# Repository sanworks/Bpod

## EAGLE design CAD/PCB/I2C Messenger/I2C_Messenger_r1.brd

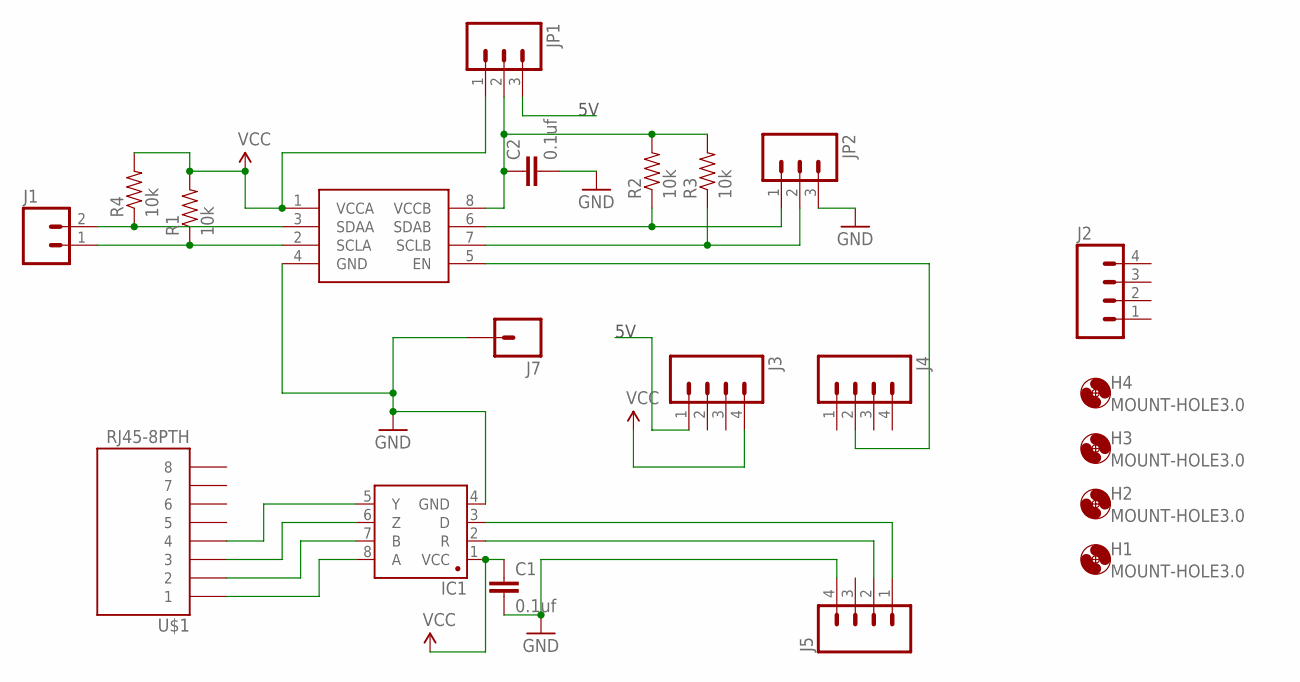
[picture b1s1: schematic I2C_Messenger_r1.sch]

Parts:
C1, C2: 0.1uf; 1206
H1, H2, H3, H4: MOUNT-HOLE3.0; 3,0
IC1: SN65HVD31DR; SO08
IC2: PCA9517; SO-08
J1: M02PTH; 1X02
J2, J3, J4, J5: M04PTH; 1X04
J7: M01PTH; 1X01
JP1: M03PTH; 1X03
JP2: M03SCREW_LOCK; SCREWTERMINAL-3.5MM-3_LOCK.007S
R1, R2, R3, R4: 10k; 1206
U$1: RJ45-8PTH; RJ45-8

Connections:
5V: J3.1, JP1.3
GND: C1.2, C2.2, IC1.4 (GND), IC2.4 (GND), J5.4, J7.1, JP2.3
unnamed: IC1.3 (D), J5.1
unnamed: IC2.2 (SCLA), J1.1, R1.1
unnamed: IC1.2 (R), J5.2
unnamed: IC1.8 (A), U$1.1
unnamed: IC1.7 (B), U$1.2
unnamed: IC1.6 (Z), U$1.3
unnamed: IC1.5 (Y), U$1.4
unnamed: IC2.3 (SDAA), J1.2, R4.1
unnamed: C2.1, IC2.8 (VCCB), JP1.2, R2.2, R3.2
unnamed: IC2.5 (EN), J4.2
unnamed: IC2.6 (SDAB), JP2.1, R2.1
unnamed: IC2.7 (SCLB), JP2.2, R3.1
VCC: C1.1, IC1.1 (VCC), IC2.1 (VCCA), J3.4, JP1.1, R1.2, R4.2

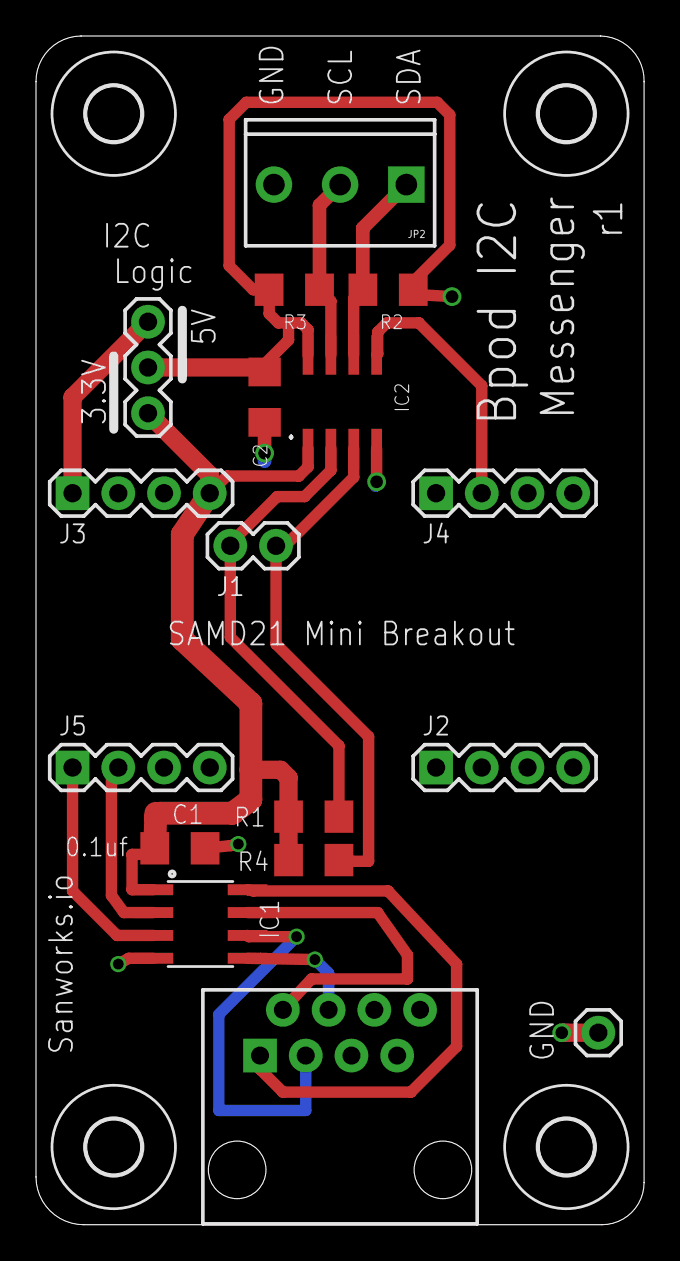
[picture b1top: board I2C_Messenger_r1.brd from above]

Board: 2 copper layers, 33.8 x 66.0 mm, 21 parts (0 on the bottom side), 15 nets.

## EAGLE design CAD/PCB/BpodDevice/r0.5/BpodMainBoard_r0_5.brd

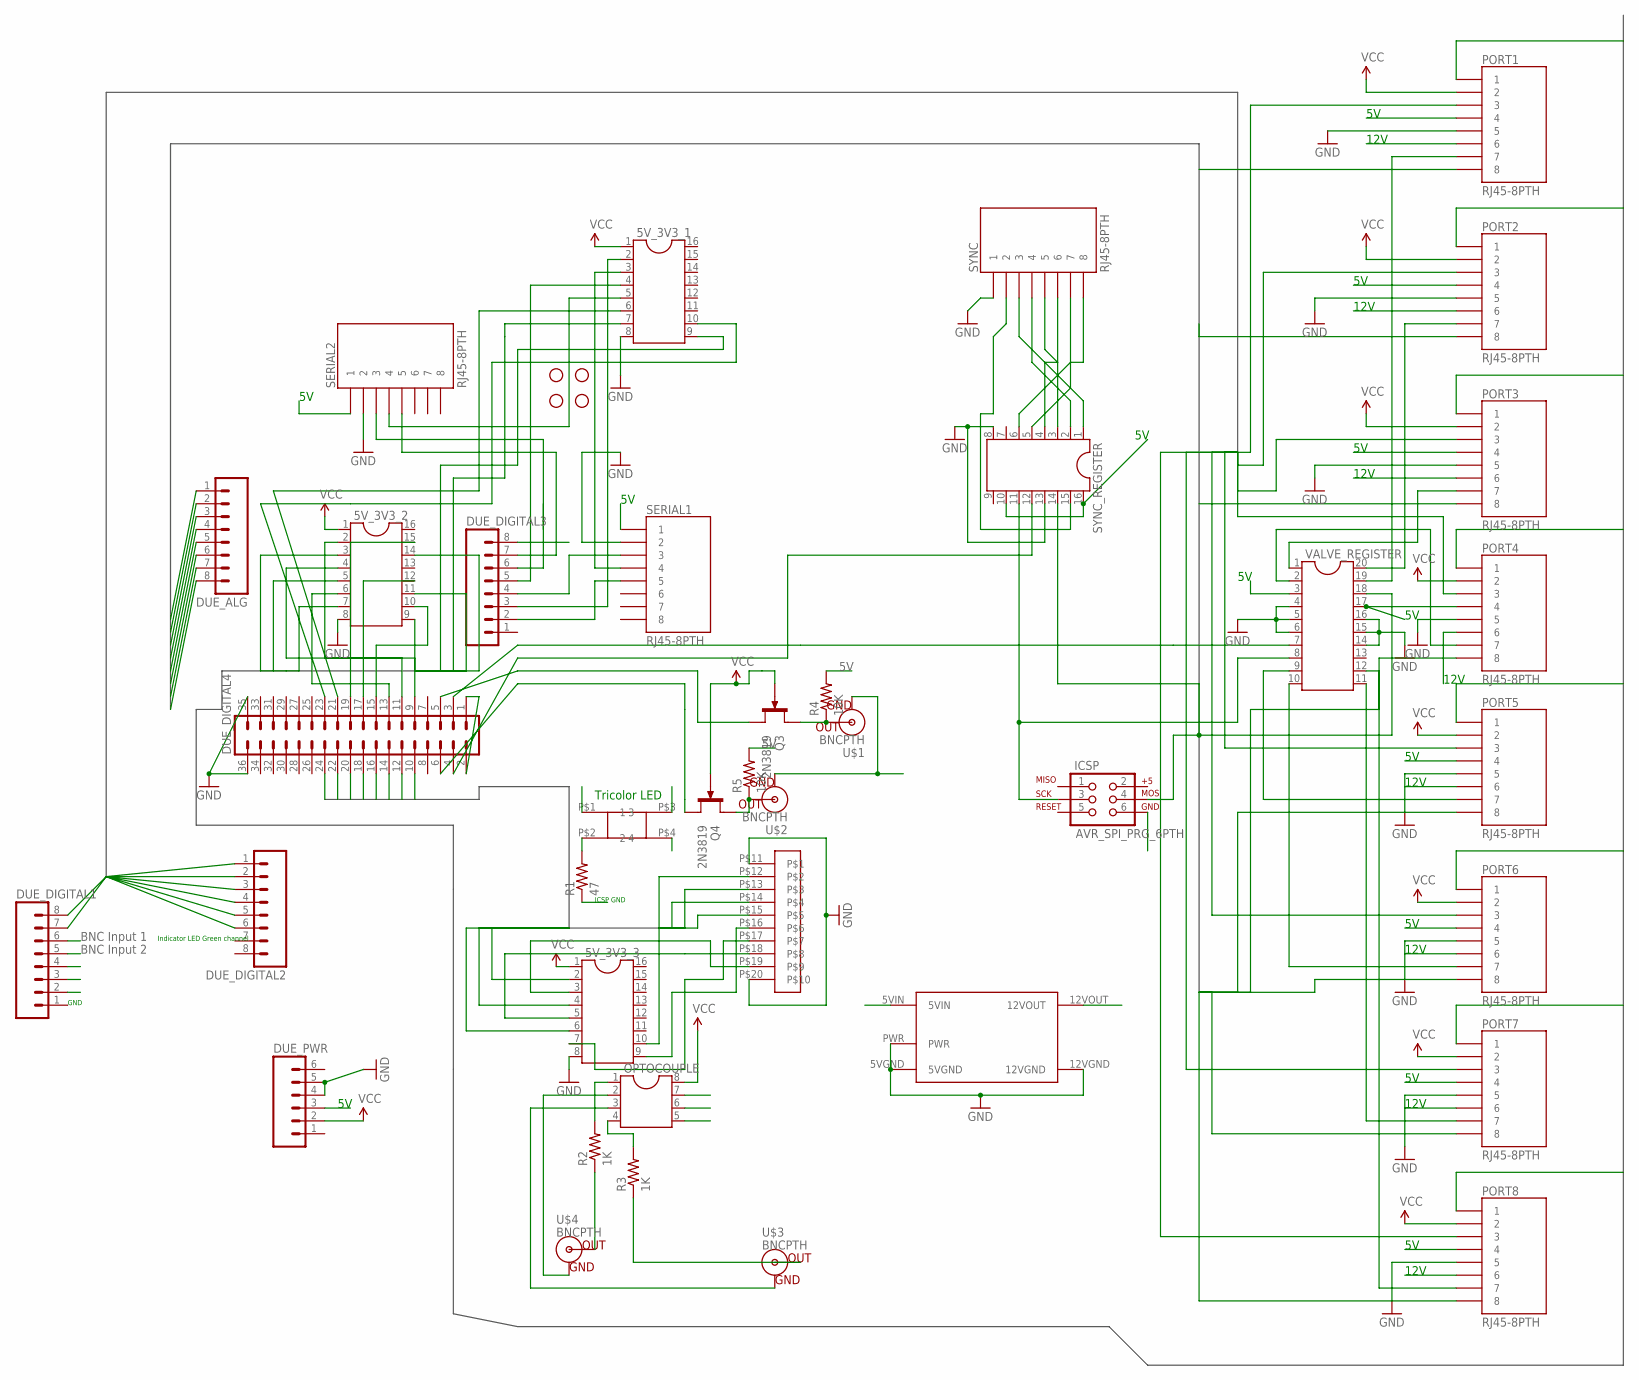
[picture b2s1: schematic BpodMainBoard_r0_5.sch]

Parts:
5V_3V3_1, 5V_3V3_2, 5V_3V3_3: DIL16
DUE_ALG: M081X08; 1X08
DUE_DIGITAL1, DUE_DIGITAL2, DUE_DIGITAL3: M081X08; 1X08
DUE_DIGITAL4: MA18-2
DUE_PWR: M06SIP; 1X06
ICSP: AVR_SPI_PRG_6PTH; 2X3
JP1, JP2, JP3, JP4: STAND-OFF
OPTOCOUPLE: DIL8; DIL08
PORT1, PORT2, PORT3, PORT4, PORT5, PORT6, PORT7, PORT8: RJ45-8PTH; RJ45-8
Q3, Q4: 2N3819; TO92F
R1: 47; AXIAL-0.3
R2, R3: 1K; AXIAL-0.3
R4, R5: 10K; AXIAL-0.3
SERIAL1, SERIAL2: RJ45-8PTH; RJ45-8
SYNC: RJ45-8PTH; RJ45-8
SYNC_REGISTER: DIL16
U$1, U$2, U$3, U$4: BNCPTH; BNC
U$5: TDK_LAMBDA_5V_TO_12V; TDK_LAMBDA_5V_12V
U$6: 10POS_SPRING_TERMINAL; 10POS_SCREW_TERMINAL
U$8: SQUARE_TRICOLOR_LED
VALVE_REGISTER: DIL20

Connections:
5V: DUE_DIGITAL4.1, DUE_DIGITAL4.2, DUE_PWR.3, PORT1.4, PORT2.4, PORT3.4, PORT4.4, PORT5.4, PORT6.4, PORT7.4, PORT8.4, R4.P$2 (2), R5.P$2 (2), SERIAL1.1, SERIAL2.1, SYNC_REGISTER.10, SYNC_REGISTER.16, U$5.5VIN, VALVE_REGISTER.3, VALVE_REGISTER.17
12V: PORT1.6, PORT2.6, PORT3.6, PORT4.6, PORT5.6, PORT6.6, PORT7.6, PORT8.6, U$5.12VOUT
ANALOG_BUS1: DUE_ALG.1, PORT1.8
ANALOG_BUS2: DUE_ALG.2, PORT2.8
ANALOG_BUS3: DUE_ALG.3, PORT3.8
ANALOG_BUS4: DUE_ALG.4, PORT4.8
ANALOG_BUS5: DUE_ALG.5, PORT5.8
ANALOG_BUS6: DUE_ALG.6, PORT6.8
ANALOG_BUS7: DUE_ALG.7, PORT7.8
ANALOG_BUS8: DUE_ALG.8, PORT8.8
BNCIN1: DUE_DIGITAL1.6, OPTOCOUPLE.7
BNCIN2: DUE_DIGITAL1.5, OPTOCOUPLE.6
DIGITAL_BUS1: 5V_3V3_2.3, PORT1.1
DIGITAL_BUS2: 5V_3V3_2.5, PORT2.1
DIGITAL_BUS3: 5V_3V3_2.7, PORT3.1
DIGITAL_BUS4: 5V_3V3_2.9, PORT4.1
DIGITAL_BUS5: 5V_3V3_2.11, PORT5.1
DIGITAL_BUS6: 5V_3V3_2.14, PORT6.1
DIGITAL_BUS7: 5V_3V3_1.7, PORT7.1
DIGITAL_BUS8: 5V_3V3_1.9, PORT8.1
DSUB_BUS1: 5V_3V3_3.2, DUE_DIGITAL4.10
DSUB_BUS2: 5V_3V3_3.4, DUE_DIGITAL4.12
DSUB_BUS3: 5V_3V3_3.6, DUE_DIGITAL4.14
DSUB_BUS4: 5V_3V3_3.10, DUE_DIGITAL4.16
DSUB_BUS5: DUE_DIGITAL4.18, U$6.P$15
DSUB_BUS6: DUE_DIGITAL4.20, U$6.P$14
DSUB_BUS7: DUE_DIGITAL4.22, U$6.P$13
DSUB_BUS8: DUE_DIGITAL4.24, U$6.P$12
GND: 5V_3V3_1.8, 5V_3V3_2.8, 5V_3V3_3.8, DUE_DIGITAL4.35, DUE_DIGITAL4.36, DUE_PWR.4, DUE_PWR.5, PORT1.5, PORT2.5, PORT3.5, PORT4.5, PORT5.5, PORT6.5, PORT7.5, PORT8.5, SERIAL1.2, SERIAL2.2, SYNC.1, SYNC_REGISTER.8, SYNC_REGISTER.13, U$5.5VGND, U$5.12VGND, U$5.PWR, U$6.P$11, U$6.P$20, VALVE_REGISTER.4, VALVE_REGISTER.5, VALVE_REGISTER.6, VALVE_REGISTER.14, VALVE_REGISTER.15, VALVE_REGISTER.16
ICSP_GND: ICSP.6, R1.P$1 (1)
LED1: DUE_DIGITAL1.4, U$8.P$3 (3)
LED2: DUE_DIGITAL1.3, U$8.P$4 (4)
LED3: DUE_DIGITAL3.8, U$8.P$1 (1)
LED_BUS1: DUE_DIGITAL1.7, PORT1.3
LED_BUS2: DUE_DIGITAL1.8, PORT2.3
LED_BUS3: DUE_DIGITAL2.1, PORT3.3
LED_BUS4: DUE_DIGITAL2.2, PORT4.3
LED_BUS5: DUE_DIGITAL2.3, PORT5.3
LED_BUS6: DUE_DIGITAL2.4, PORT6.3
LED_BUS7: DUE_DIGITAL2.5, PORT7.3
LED_BUS8: DUE_DIGITAL2.6, PORT8.3
unnamed: R2.P$1 (1), U$4.S (OUT)
unnamed: R3.P$1 (1), U$3.S (OUT)
unnamed: OPTOCOUPLE.1, R2.P$2 (2)
unnamed: OPTOCOUPLE.4, R3.P$2 (2)
unnamed: OPTOCOUPLE.2, U$4.GND
unnamed: OPTOCOUPLE.3, U$3.GND
unnamed: Q3.D, R4.P$1 (1), U$1.S (OUT)
unnamed: Q4.D, R5.P$1 (1), U$2.S (OUT)
unnamed: PORT1.7, VALVE_REGISTER.19
unnamed: PORT2.7, VALVE_REGISTER.20
unnamed: PORT3.7, VALVE_REGISTER.1
unnamed: PORT4.7, VALVE_REGISTER.2
unnamed: PORT5.7, VALVE_REGISTER.9
unnamed: PORT6.7, VALVE_REGISTER.10
unnamed: PORT7.7, VALVE_REGISTER.11
unnamed: PORT8.7, VALVE_REGISTER.12
unnamed: SYNC.2, SYNC_REGISTER.15
unnamed: SYNC.3, SYNC_REGISTER.1
unnamed: SYNC.4, SYNC_REGISTER.2
unnamed: DUE_DIGITAL4.3, VALVE_REGISTER.7
unnamed: SYNC.5, SYNC_REGISTER.3
unnamed: SYNC.6, SYNC_REGISTER.4
unnamed: SYNC.7, SYNC_REGISTER.5
unnamed: SYNC.8, SYNC_REGISTER.6
unnamed: R1.P$2 (2), U$8.P$2 (2)
unnamed: DUE_DIGITAL4.5, Q3.S
unnamed: DUE_DIGITAL4.4, SYNC_REGISTER.12
unnamed: DUE_DIGITAL4.6, Q4.S
unnamed: 5V_3V3_1.3, SERIAL1.4
unnamed: 5V_3V3_1.2, DUE_DIGITAL3.3
unnamed: DUE_DIGITAL3.4, SERIAL1.3
unnamed: 5V_3V3_1.5, SERIAL2.4
unnamed: 5V_3V3_1.4, DUE_DIGITAL3.5
unnamed: DUE_DIGITAL3.2, SERIAL1.5
unnamed: 5V_3V3_1.6, DUE_DIGITAL4.21
unnamed: DUE_DIGITAL3.6, SERIAL2.3
unnamed: 5V_3V3_1.10, DUE_DIGITAL4.23
unnamed: DUE_DIGITAL3.7, SERIAL2.5
unnamed: 5V_3V3_2.2, DUE_DIGITAL4.9
unnamed: 5V_3V3_2.4, DUE_DIGITAL4.11
unnamed: 5V_3V3_2.6, DUE_DIGITAL4.13
unnamed: 5V_3V3_2.10, DUE_DIGITAL4.15
unnamed: 5V_3V3_2.12, DUE_DIGITAL4.17
unnamed: 5V_3V3_2.15, DUE_DIGITAL4.19
unnamed: 5V_3V3_3.3, U$6.P$19
unnamed: 5V_3V3_3.5, U$6.P$18
unnamed: 5V_3V3_3.7, U$6.P$17
unnamed: 5V_3V3_3.9, U$6.P$16
SPI_CLK: ICSP.3, SYNC_REGISTER.11, VALVE_REGISTER.8
SPI_DATA: ICSP.4, SYNC_REGISTER.14, VALVE_REGISTER.18
UPPER_GND: DUE_DIGITAL1.2, OPTOCOUPLE.5, U$1.GND, U$2.GND
VCC: 5V_3V3_1.1, 5V_3V3_2.1, 5V_3V3_3.1, DUE_PWR.2, OPTOCOUPLE.8, PORT1.2, PORT2.2, PORT3.2, PORT4.2, PORT5.2, PORT6.2, PORT7.2, PORT8.2, Q3.G, Q4.G

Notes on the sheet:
12V
BNC Input 1
BNC Input 2
Indicator LED Green channel
Tricolor LED
ICSP GND
GND

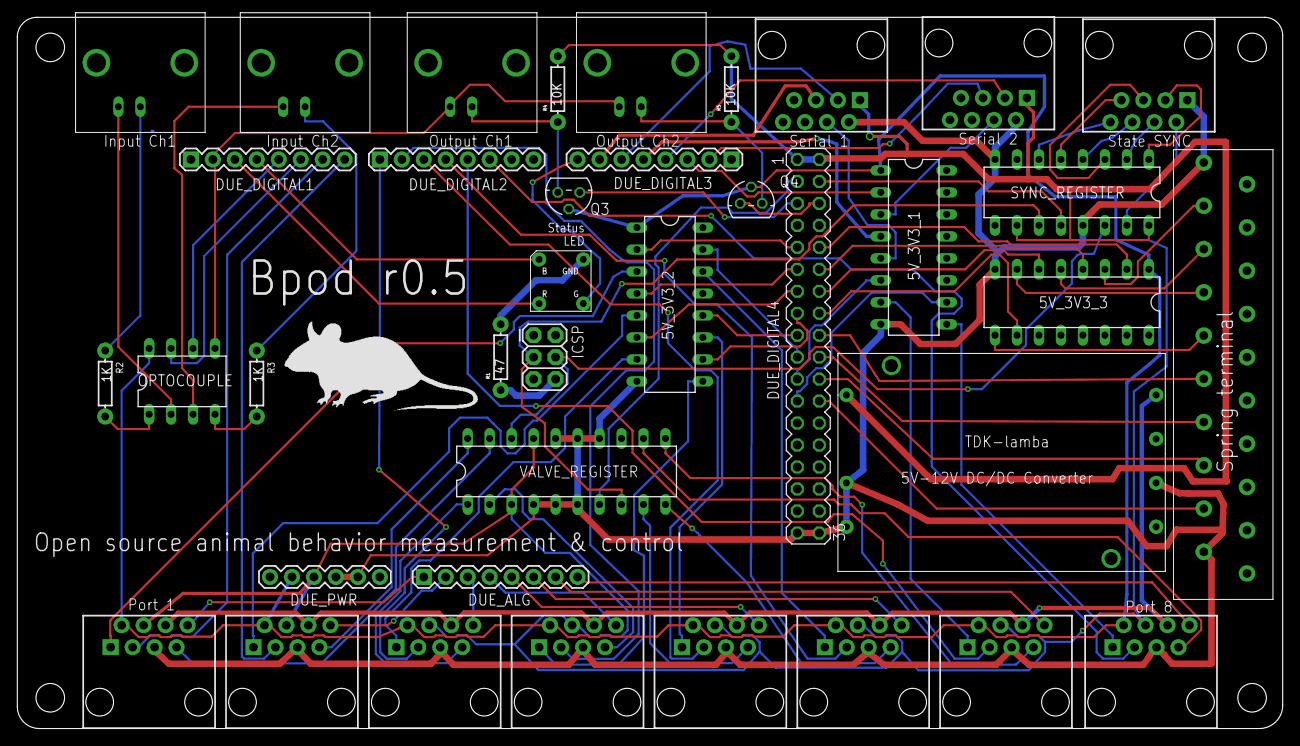
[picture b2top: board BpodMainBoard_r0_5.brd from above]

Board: 2 copper layers, 146.3 x 82.2 mm, 43 parts (0 on the bottom side), 93 nets.

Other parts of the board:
U$7: MOUSELOGO

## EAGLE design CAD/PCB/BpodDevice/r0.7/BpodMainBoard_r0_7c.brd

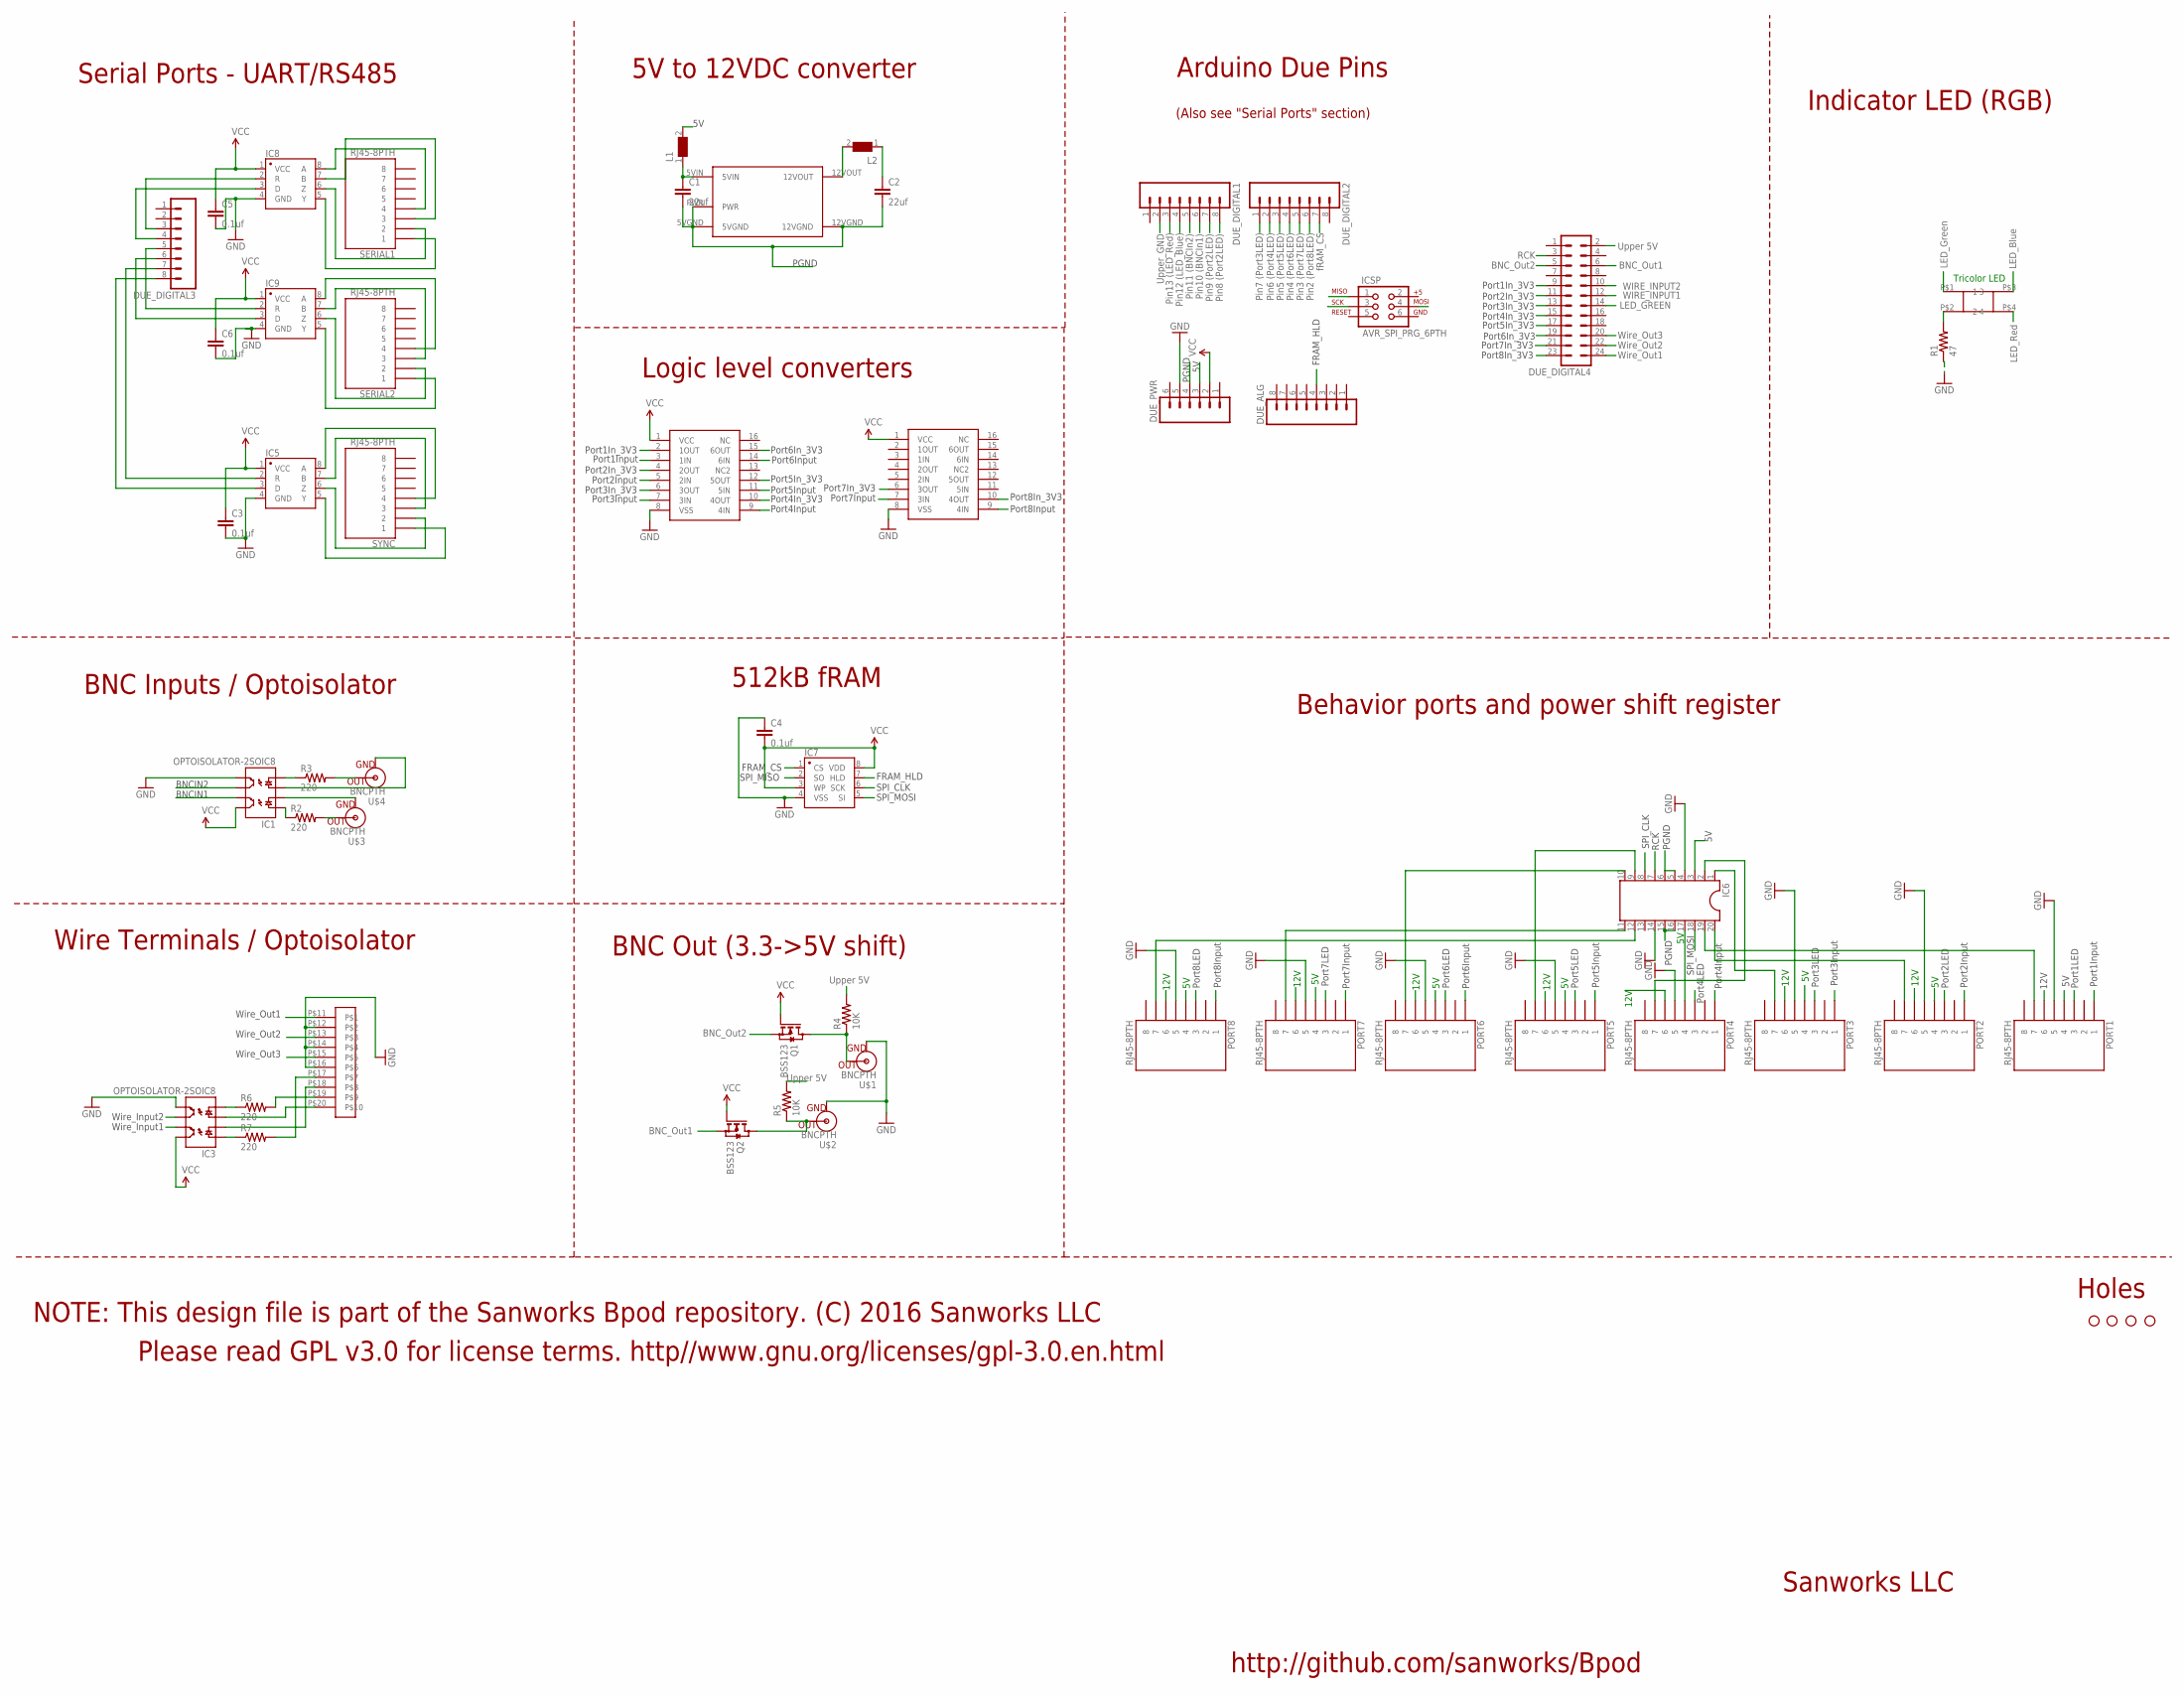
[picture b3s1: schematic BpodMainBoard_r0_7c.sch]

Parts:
C1, C2: 22uf; 1206
C3, C4, C5, C6: 0.1uf; 1206
DUE_ALG: M081X08; 1X08
DUE_DIGITAL1, DUE_DIGITAL2, DUE_DIGITAL3: M081X08; 1X08
DUE_DIGITAL4: MA12-2
DUE_PWR: M06SIP; 1X06
IC1, IC3: OPTOISOLATOR-2SOIC8; SO08-2
IC2, IC4: CD4050; SO16
IC5, IC8, IC9: SN65HVD31DR; SO08
IC6: DIL20
IC7: CY15B104Q-SXI; SO08-UNIVERSAL
ICSP: AVR_SPI_PRG_6PTH; 2X3
JP1, JP2, JP3, JP4: STAND-OFF
L1: WE-CBF-742792118_1206; 1206
L2: WE-CBF-742792118_1206; 1206; MPN 742792118
PORT1, PORT2, PORT3, PORT4, PORT5, PORT6, PORT7, PORT8: RJ45-8PTH; RJ45-8
Q1, Q2: BSS123; SOT23
R1: 47; 1206
R2, R3, R6, R7: 220; 1206
R4, R5: 10K; 1206
SERIAL1, SERIAL2: RJ45-8PTH; RJ45-8
SYNC: RJ45-8PTH; RJ45-8
U$1, U$2, U$3, U$4: BNCPTH; BNC
U$5: TDK_LAMBDA_5V_TO_12V; TDK_LAMBDA_5V_12V
U$6: 10POS_SPRING_TERMINAL; 10POS_SCREW_TERMINAL
U$8: SQUARE_TRICOLOR_LED

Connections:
5V: DUE_PWR.3, IC6.3, IC6.17, L1.2, PORT1.4, PORT2.4, PORT3.4, PORT4.4, PORT5.4, PORT6.4, PORT7.4, PORT8.4
12V: C2.1, L2.1, PORT1.6, PORT2.6, PORT3.6, PORT4.6, PORT5.6, PORT6.6, PORT7.6, PORT8.6
BNCIN1: DUE_DIGITAL1.6, IC1.7 (EM1)
BNCIN2: DUE_DIGITAL1.5, IC1.6 (CL2)
BNC_OUT1: DUE_DIGITAL4.6, Q2.2 (S)
BNC_OUT2: DUE_DIGITAL4.5, Q1.2 (S)
FRAM_CS: DUE_DIGITAL2.7, IC7.1 (CS)
FRAM_HLD: DUE_ALG.4, IC7.7 (HLD)
GND: C3.2, C5.2, C6.2, DUE_PWR.5, IC1.5 (EM2), IC2.8 (VSS), IC3.5 (EM2), IC4.8 (VSS), IC5.4 (GND), IC6.4, IC6.14, IC7.4 (VSS), IC8.4 (GND), IC9.4 (GND), PORT1.5, PORT2.5, PORT3.5, PORT4.5, PORT5.5, PORT6.5, PORT7.5, PORT8.5, R1.1, U$1.GND, U$2.GND, U$6.P$12, U$6.P$14, U$6.P$16
LED_BLUE: DUE_DIGITAL1.4, U$8.P$3 (3)
LED_GREEN: DUE_DIGITAL4.14, U$8.P$1 (1)
LED_RED: DUE_DIGITAL1.3, U$8.P$4 (4)
MOSI: IC6.18, IC7.5 (SI), ICSP.4
unnamed: R3.2, U$4.S (OUT)
unnamed: R2.2, U$3.S (OUT)
unnamed: IC1.3 (A2), U$4.GND
unnamed: IC1.2 (C1), U$3.GND
unnamed: R6.2, U$6.P$19
unnamed: Q1.3 (D), R4.1, U$1.S (OUT)
unnamed: Q2.3 (D), R5.1, U$2.S (OUT)
unnamed: IC6.19, PORT1.7
unnamed: IC6.20, PORT2.7
unnamed: IC6.1, PORT3.7
unnamed: IC6.2, PORT4.7
unnamed: IC6.9, PORT5.7
unnamed: IC6.10, PORT6.7
unnamed: IC6.11, PORT7.7
unnamed: IC6.12, PORT8.7
unnamed: IC5.8 (A), SYNC.4
unnamed: IC5.7 (B), SYNC.3
unnamed: IC5.6 (Z), SYNC.2
unnamed: IC5.5 (Y), SYNC.1
unnamed: DUE_DIGITAL3.7, IC5.2 (R)
unnamed: IC3.4 (C2), R6.1
unnamed: IC3.1 (A1), R7.1
unnamed: R1.2, U$8.P$2 (2)
unnamed: DUE_DIGITAL3.8, IC5.3 (D)
unnamed: IC8.8 (A), SERIAL1.4
unnamed: IC8.7 (B), SERIAL1.3
unnamed: IC8.6 (Z), SERIAL1.2
unnamed: IC8.5 (Y), SERIAL1.1
unnamed: IC9.8 (A), SERIAL2.4
unnamed: IC9.7 (B), SERIAL2.3
unnamed: IC9.6 (Z), SERIAL2.2
unnamed: IC9.5 (Y), SERIAL2.1
unnamed: DUE_DIGITAL3.3, IC8.2 (R)
unnamed: IC3.3 (A2), U$6.P$20
unnamed: R7.2, U$6.P$17
unnamed: IC3.2 (C1), U$6.P$18
unnamed: C1.1, L1.1, U$5.5VIN
unnamed: L2.2, U$5.12VOUT
unnamed: DUE_DIGITAL3.4, IC8.3 (D)
unnamed: DUE_DIGITAL3.5, IC9.2 (R)
unnamed: DUE_DIGITAL3.6, IC9.3 (D)
unnamed: IC1.1 (A1), R2.1
unnamed: IC1.4 (C2), R3.1
PGND: C1.2, C2.2, DUE_PWR.4, IC6.5, IC6.6, IC6.15, IC6.16, U$5.5VGND, U$5.12VGND, U$5.PWR
PORT1INPUT: IC4.3 (1IN), PORT1.1
PORT1IN_3V3: DUE_DIGITAL4.9, IC4.2 (1OUT)
PORT1LED: DUE_DIGITAL1.7, PORT1.3
PORT2INPUT: IC4.5 (2IN), PORT2.1
PORT2IN_3V3: DUE_DIGITAL4.11, IC4.4 (2OUT)
PORT2LED: DUE_DIGITAL1.8, PORT2.3
PORT3INPUT: IC4.7 (3IN), PORT3.1
PORT3IN_3V3: DUE_DIGITAL4.13, IC4.6 (3OUT)
PORT3LED: DUE_DIGITAL2.1, PORT3.3
PORT4INPUT: IC4.9 (4IN), PORT4.1
PORT4IN_3V3: DUE_DIGITAL4.15, IC4.10 (4OUT)
PORT4LED: DUE_DIGITAL2.2, PORT4.3
PORT5INPUT: IC4.11 (5IN), PORT5.1
PORT5IN_3V3: DUE_DIGITAL4.17, IC4.12 (5OUT)
PORT5LED: DUE_DIGITAL2.3, PORT5.3
PORT6INPUT: IC4.14 (6IN), PORT6.1
PORT6IN_3V3: DUE_DIGITAL4.19, IC4.15 (6OUT)
PORT6LED: DUE_DIGITAL2.4, PORT6.3
PORT7INPUT: IC2.7 (3IN), PORT7.1
PORT7IN_3V3: DUE_DIGITAL4.21, IC2.6 (3OUT)
PORT7LED: DUE_DIGITAL2.5, PORT7.3
PORT8INPUT: IC2.9 (4IN), PORT8.1
PORT8IN_3V3: DUE_DIGITAL4.23, IC2.10 (4OUT)
PORT8LED: DUE_DIGITAL2.6, PORT8.3
RCK: DUE_DIGITAL4.3, IC6.7
SPI_CLK: IC6.8, IC7.6 (SCK), ICSP.3
SPI_MISO: IC7.2 (SO), ICSP.1
UPPER_5V: DUE_DIGITAL4.2, R4.2, R5.2
UPPER_GND: DUE_DIGITAL1.2
VCC: C3.1, C4.2, C5.1, C6.1, DUE_PWR.2, IC1.8 (CL1), IC2.1 (VCC), IC3.8 (CL1), IC4.1 (VCC), IC5.1 (VCC), IC7.3 (WP), IC7.8 (VDD), IC8.1 (VCC), IC9.1 (VCC), Q1.1 (G), Q2.1 (G)
WIREOUT3: DUE_DIGITAL4.20, U$6.P$15
WIRE_INPUT1: DUE_DIGITAL4.12, IC3.7 (EM1)
WIRE_INPUT2: DUE_DIGITAL4.10, IC3.6 (CL2)
WIRE_OUT1: DUE_DIGITAL4.24, U$6.P$11
WIRE_OUT2: DUE_DIGITAL4.22, U$6.P$13

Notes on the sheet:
12V
Pin10 (BNCIn1)
Pin11 (BNCIn2)
Upper 5V
Tricolor LED
BNCIN1
BNCIN2
PGND
Pin12 (LED_Blue)
Pin13 (LED_Red)
Upper_GND
Pin8 (Port2LED)
Pin9 (Port2LED)
Pin7 (Port3LED)
Pin6 (Port4LED)
Pin5 (Port5LED)
Pin4 (Port6LED)
Pin3 (Port7LED)
Pin2 (Port8LED)
fRAM_CS
Port1LED
Serial Ports - UART/RS485
BNC Inputs / Optoisolator
Port2LED
5V to 12VDC converter
Sanworks LLC
Port3LED
Port4LED
Port5LED
Port6LED
Port7LED
Port8LED
Logic level converters
Port1Input
Port2Input
Port3Input
Port4Input
Port5Input
Port6Input
Port7Input

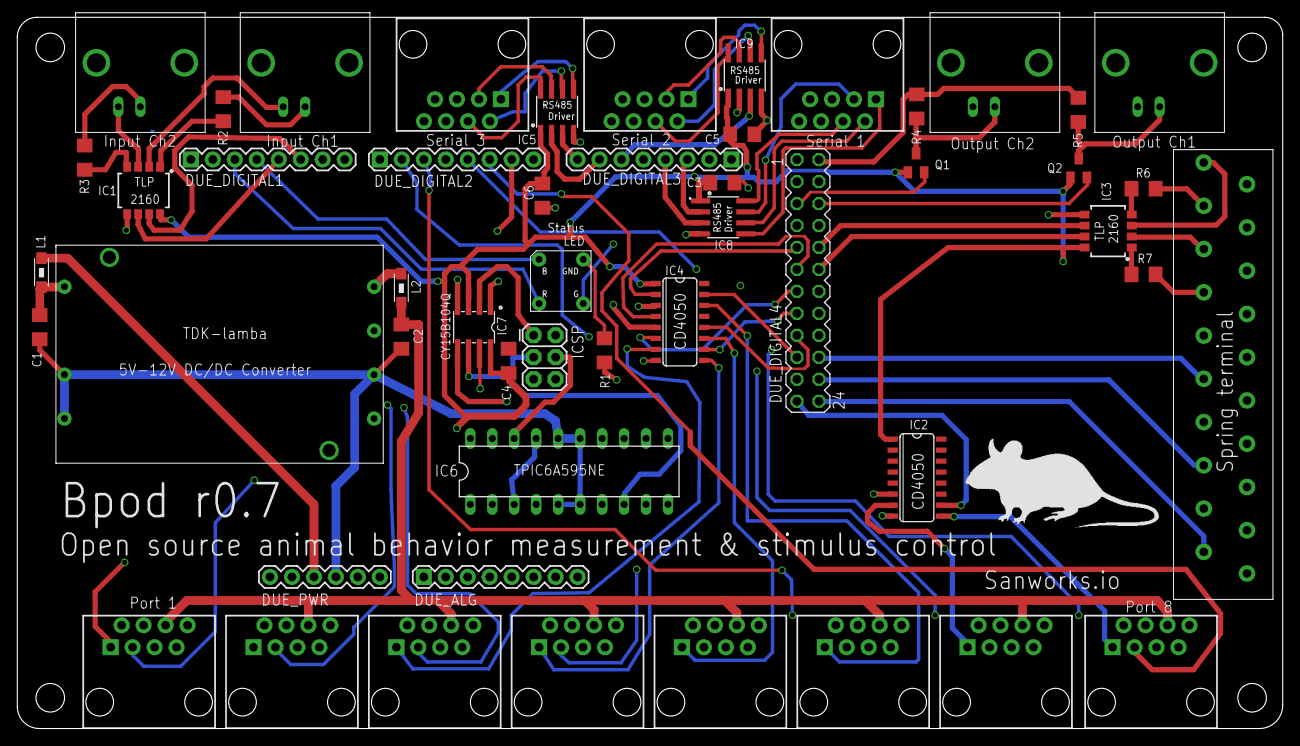
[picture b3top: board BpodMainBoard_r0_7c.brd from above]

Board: 4 copper layers, 146.3 x 82.2 mm, 56 parts (0 on the bottom side), 91 nets.

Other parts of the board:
U$7: MOUSELOGO

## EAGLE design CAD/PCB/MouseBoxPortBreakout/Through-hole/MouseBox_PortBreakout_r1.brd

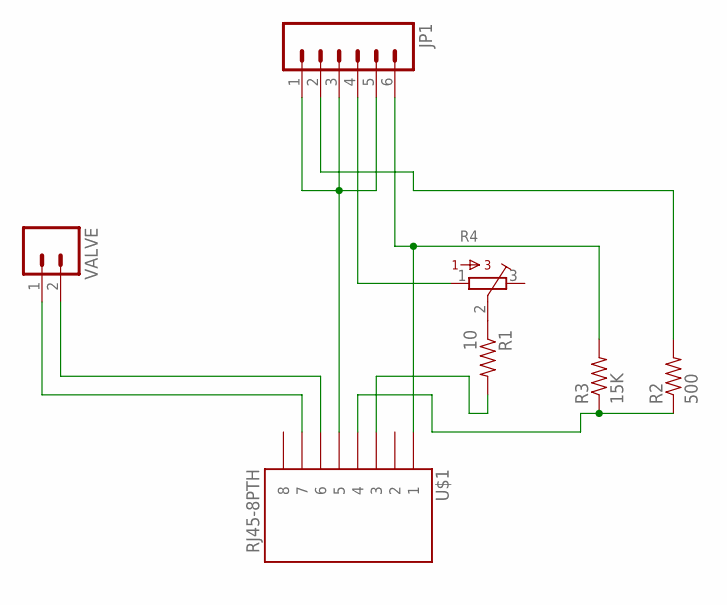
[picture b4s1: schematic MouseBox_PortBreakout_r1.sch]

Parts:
JP1: M063.5MM-6; SCREWTERMINAL-3.5MM-6
R1: 10; AXIAL-0.3
R2: 500; AXIAL-0.3
R3: 15K; AXIAL-0.3
R4: 3362R
U$1: RJ45-8PTH; RJ45-8
VALVE: M023.5MM_LOCK; SCREWTERMINAL-3.5MM-2_LOCK

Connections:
GND: JP1.1, JP1.3, JP1.5, U$1.5
unnamed: JP1.6, R3.P$2 (2), U$1.1
unnamed: R2.P$1 (1), R3.P$1 (1), U$1.4
unnamed: JP1.2, R2.P$2 (2)
unnamed: R1.P$1 (1), R4.2
unnamed: U$1.6, VALVE.2
unnamed: U$1.7, VALVE.1
unnamed: JP1.4, R4.1
unnamed: R1.P$2 (2), U$1.3

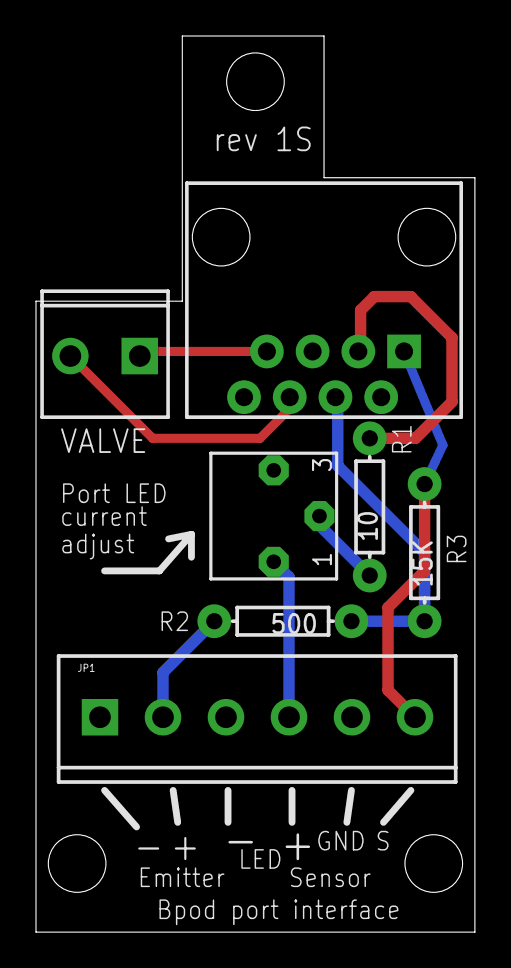
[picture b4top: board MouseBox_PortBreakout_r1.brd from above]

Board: 2 copper layers, 24.4 x 49.8 mm, 7 parts (0 on the bottom side), 9 nets.

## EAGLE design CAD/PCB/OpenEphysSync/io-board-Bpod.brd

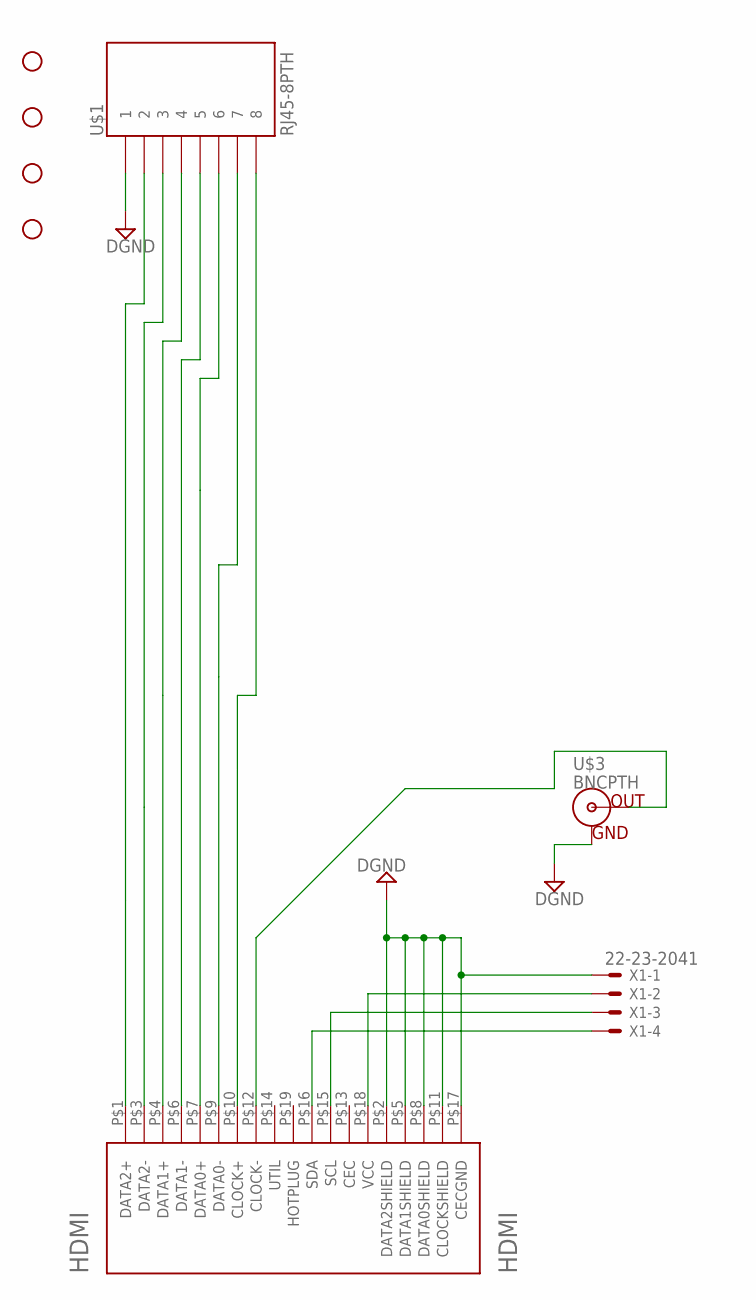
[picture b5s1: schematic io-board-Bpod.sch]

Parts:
HDMI: HDMI; HDMI_A
STANDOFF1, STANDOFF2, STANDOFF3, STANDOFF4: STAND-OFF
U$1: RJ45-8PTH; RJ45-8
U$3: BNCPTH; BNC
X1: 22-23-2041

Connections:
CH6: HDMI.P$9 (DATA0-), U$1.7
DGND: HDMI.P$2 (DATA2SHIELD), HDMI.P$5 (DATA1SHIELD), HDMI.P$8 (DATA0SHIELD), HDMI.P$11 (CLOCKSHIELD), HDMI.P$17 (CECGND), U$1.1, U$3.GND, X1.1
I2C_CLK: HDMI.P$15 (SCL), X1.3
I2C_DAT: HDMI.P$16 (SDA), X1.4
unnamed: HDMI.P$12 (CLOCK-), U$3.S (OUT)
unnamed: HDMI.P$4 (DATA1+), U$1.4
unnamed: HDMI.P$3 (DATA2-), U$1.3
unnamed: HDMI.P$1 (DATA2+), U$1.2
unnamed: HDMI.P$7 (DATA0+), U$1.6
unnamed: HDMI.P$10 (CLOCK+), U$1.8
unnamed: HDMI.P$6 (DATA1-), U$1.5
VCC: HDMI.P$18 (VCC), X1.2

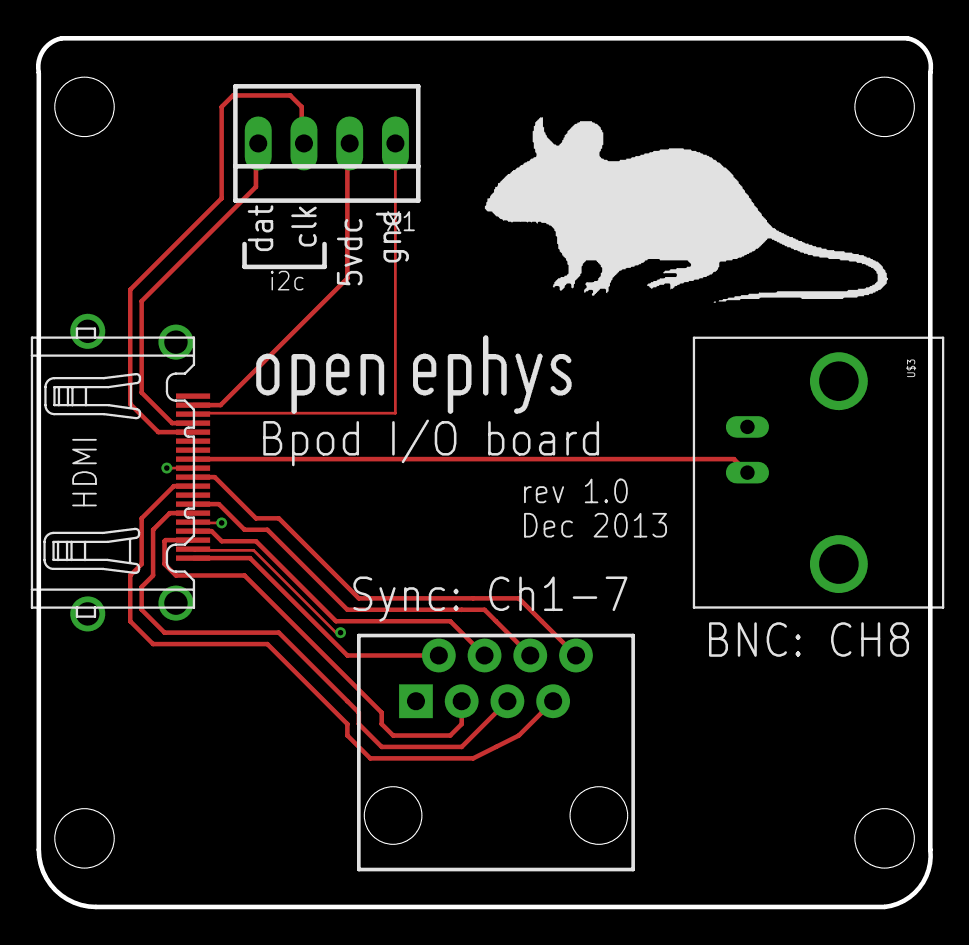
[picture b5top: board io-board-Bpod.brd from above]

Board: 4 copper layers, 49.6 x 48.3 mm, 10 parts (0 on the bottom side), 12 nets.

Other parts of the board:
U$2: OPEN_EPHYS_LOGO
U$4: MOUSELOGO

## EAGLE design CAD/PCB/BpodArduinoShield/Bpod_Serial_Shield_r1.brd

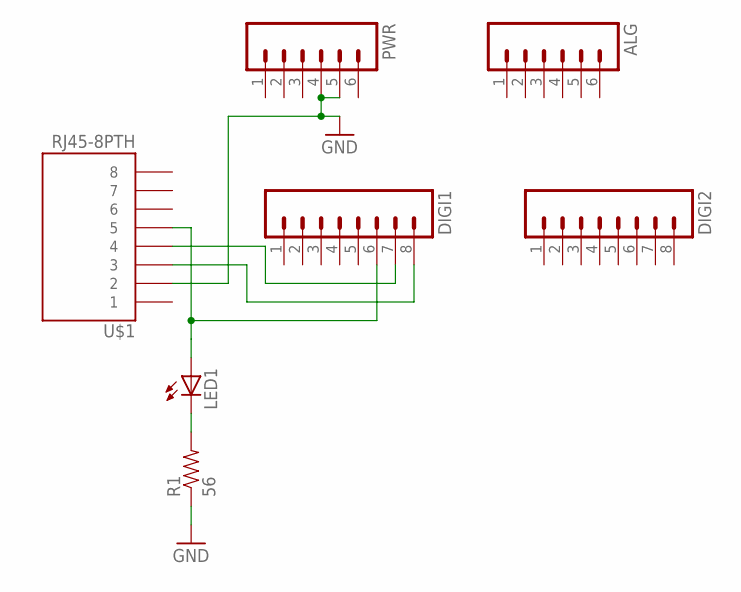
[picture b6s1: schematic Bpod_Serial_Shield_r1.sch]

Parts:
ALG: M06LONGPADS; 1X06_LONGPADS
DIGI1, DIGI2: M08LONGPADS; 1X08_LONGPADS
LED1: LED3MM
PWR: M06LONGPADS; 1X06_LONGPADS
R1: 56; AXIAL-0.3
U$1: RJ45-8PTH; RJ45-8

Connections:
GND: PWR.4, PWR.5, R1.P$1 (1), U$1.2
unnamed: DIGI1.8, U$1.3
unnamed: DIGI1.7, U$1.4
unnamed: DIGI1.6, LED1.A, U$1.5
unnamed: LED1.K (C), R1.P$2 (2)

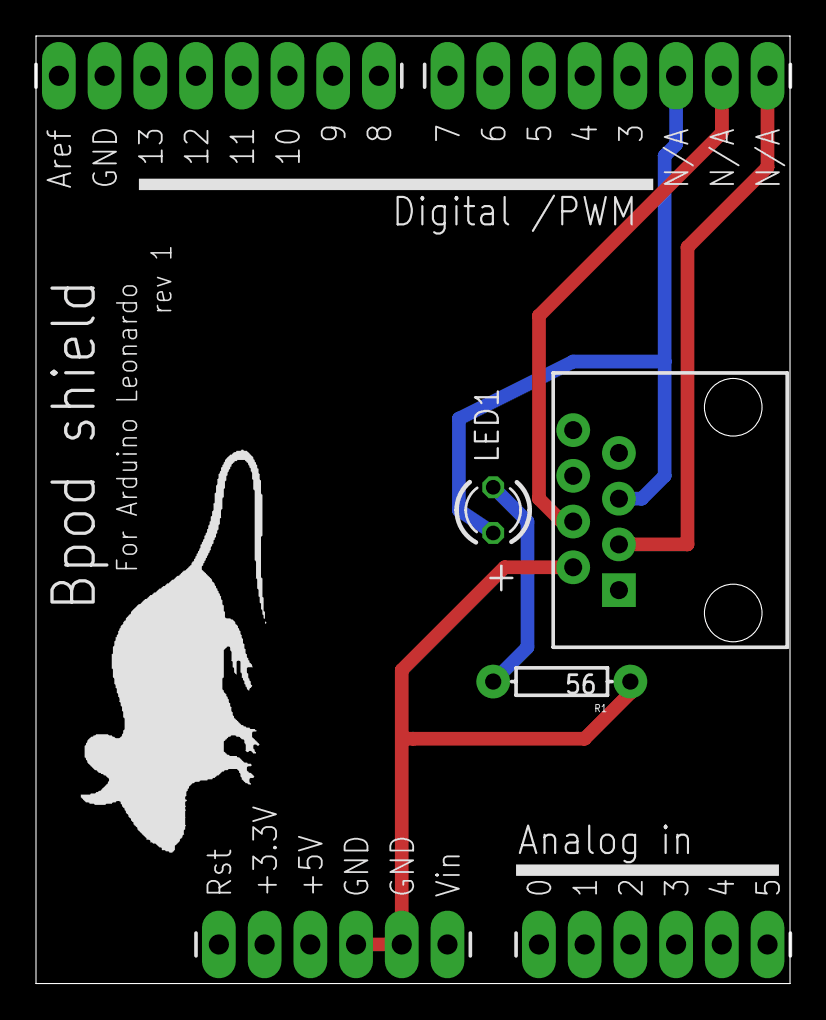
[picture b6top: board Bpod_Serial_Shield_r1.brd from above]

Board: 4 copper layers, 41.9 x 52.6 mm, 8 parts (0 on the bottom side), 5 nets.

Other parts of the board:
U$2: MOUSELOGO

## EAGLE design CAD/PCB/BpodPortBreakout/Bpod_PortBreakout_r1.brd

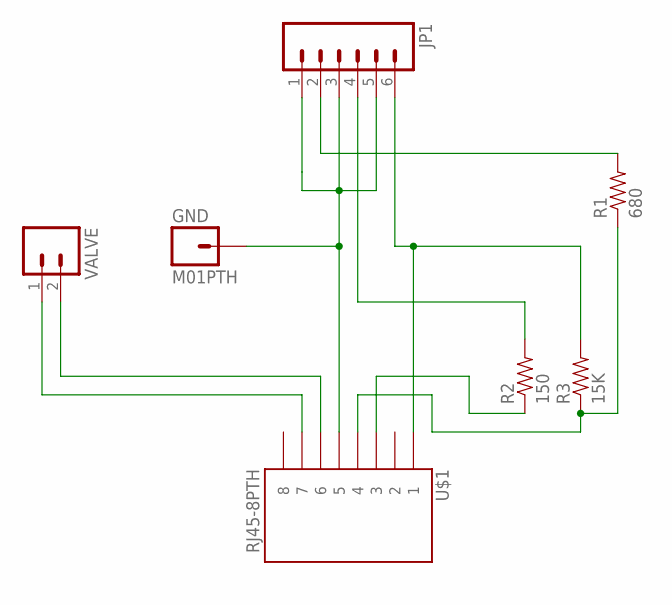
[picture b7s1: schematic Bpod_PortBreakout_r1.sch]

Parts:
GND: M01PTH; 1X01
JP1: M063.5MM-6; SCREWTERMINAL-3.5MM-6
R1: 680; AXIAL-0.4
R2: 150; AXIAL-0.4
R3: 15K; AXIAL-0.4
U$1: RJ45-8PTH; RJ45-8
VALVE: M023.5MM_LOCK; SCREWTERMINAL-3.5MM-2_LOCK

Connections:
unnamed: JP1.6, R3.P$2 (2), U$1.1
unnamed: R1.P$1 (1), R3.P$1 (1), U$1.4
unnamed: JP1.2, R1.P$2 (2)
unnamed: GND.1, JP1.1, JP1.3, JP1.5, U$1.5
unnamed: U$1.6, VALVE.2
unnamed: U$1.7, VALVE.1
unnamed: JP1.4, R2.P$2 (2)
unnamed: R2.P$1 (1), U$1.3

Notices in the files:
CAD/PCB/BpodDevice/r0.7/BpodMainBoard_r0_7c.sch:
Please read GPL v3.0 for license terms. http//www.gnu.org/licenses/gpl-3.0.en.html
NOTE: This design file is part of the Sanworks Bpod repository. (C) 2016 Sanworks LLC
parts and their libraries:
SparkFun: Licensing: CC v3.0 Share-Alike You are welcome to use this library for commercial purposes.
SparkFun-DiscreteSemi: Licensing: Creative Commons ShareAlike 4.0 International - https://creativecommons.org/licenses/by-sa/4.0
